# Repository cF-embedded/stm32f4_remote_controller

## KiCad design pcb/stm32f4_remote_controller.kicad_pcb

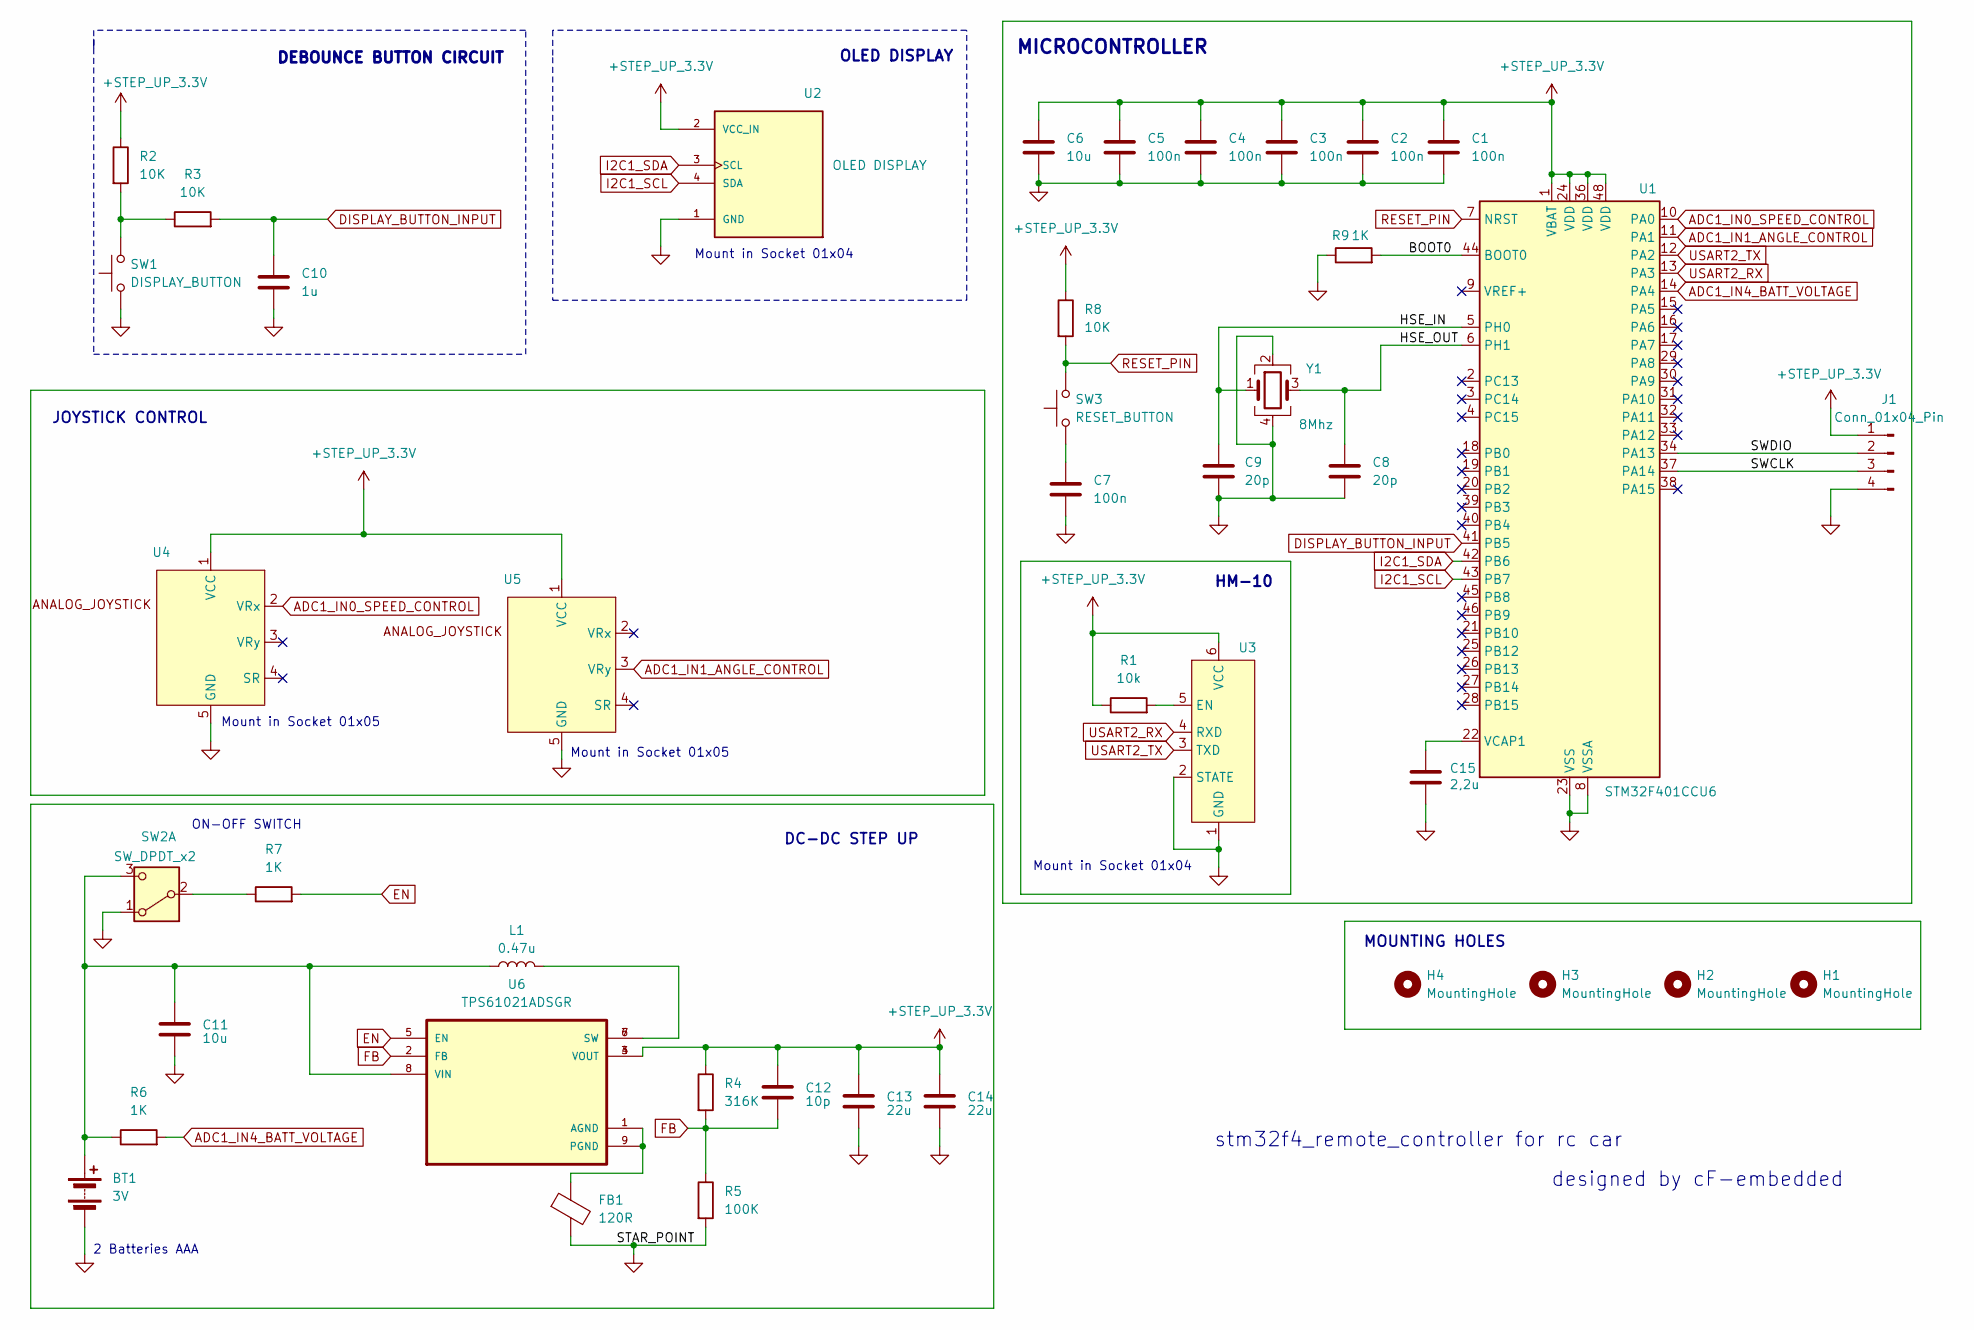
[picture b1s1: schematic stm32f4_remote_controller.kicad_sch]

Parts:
BT1: 3V; PhoenixContact_GMSTBA_2,5_2-G-7,62_1x02_P7.62mm_Horizontal
C1, C2, C3, C4, C5, C7: 100n; C_0402_1005Metric
C6, C11: 10u; C_0603_1608Metric
C8, C9: 20p; C_0402_1005Metric
C10: 1u; C_0603_1608Metric
C12: 10p; C_0402_1005Metric
C13, C14: 22u; C_0805_2012Metric
C15: 2,2u; C_0603_1608Metric
FB1: 120R; L_0603_1608Metric
H1, H2, H3, H4: MountingHole; MountingHole_2.5mm
J1: Conn_01x04_Pin; PinHeader_1x04_P2.54mm_Vertical
L1: 0.47u; L_1206_3216Metric
R1: 10k; R_0402_1005Metric
R2, R3, R8: 10K; R_0402_1005Metric
R4: 316K; R_0805_2012Metric
R5: 100K; R_0805_2012Metric
R6, R7, R9: 1K; R_0402_1005Metric
SW1: DISPLAY_BUTTON; PinHeader_1x02_P2.54mm_Vertical
SW2: SW_DPDT_x2; SW_CK_JS202011AQN_DPDT_Angled
SW3: RESET_BUTTON; SW_PUSH_6mm
U1: STM32F401CCU6; QFN-48-1EP_7x7mm_P0.5mm_EP5.6x5.6mm
U2: OLED DISPLAY; PinHeader_1x04_P2.54mm_Vertical; PARTREV 2018-09-10
U3: Molex_SL_171971-0006_1x06_P2.54mm_Vertical
U4, U5: PinHeader_1x05_P2.54mm_Vertical
U6: TPS61021ADSGR; SON50P200X200X80-9N
Y1: 8Mhz; Crystal_SMD_5032-4Pin_5.0x3.2mm

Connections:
+STEP_UP_3.3V: C1.1, C2.1, C3.1, C4.1, C5.1, C6.1, C12.1, C13.1, C14.1, J1.1, R1.1, R2.1, R4.1, R8.1, U1.1 (VBAT), U1.24 (VDD), U1.36 (VDD), U1.48 (VDD), U2.2 (VCC_IN), U3.6 (VCC), U4.1 (VCC), U5.1 (VCC), U6.3 (VOUT), U6.4 (VOUT)
/BOOT0: R9.2, U1.44 (BOOT0)
/HSE_IN: C9.1, U1.5 (PH0), Y1.1
/HSE_OUT: C8.1, U1.6 (PH1), Y1.3
/SWCLK: J1.3, U1.37 (PA14)
/SWDIO: J1.2, U1.34 (PA13)
ADC1_IN0_SPEED_CONTROL: U1.10 (PA0), U4.2 (VRx)
ADC1_IN1_ANGLE_CONTROL: U1.11 (PA1), U5.3 (VRy)
ADC1_IN4_BATT_VOLTAGE: R6.2, U1.14 (PA4)
DISPLAY_BUTTON_INPUT: C10.1, R3.2, U1.41 (PB5)
EN: R7.2, U6.5 (EN)
FB: C12.2, R4.2, R5.1, U6.2 (FB)
GND: BT1.2 (-), C1.2, C2.2, C3.2, C4.2, C5.2, C6.2, C7.2, C8.2, C9.2, C10.2, C11.2, C13.2, C14.2, C15.2, FB1.2, J1.4, R5.2, R9.1, SW1.1, SW2.1 (A), U1.8 (VSSA), U1.23 (VSS), U1.35 (VSS), U1.47 (VSS), U1.49 (VSS), U2.1 (GND), U3.1 (GND), U3.2 (STATE), U4.5 (GND), U5.5 (GND), Y1.2, Y1.4
I2C1_SCL: U1.43 (PB7), U2.4 (SDA)
I2C1_SDA: U1.42 (PB6), U2.3 (SCL)
unnamed: BT1.1 (+), C11.1, L1.1, R6.1, SW2.3 (C), U6.8 (VIN)
unnamed: C7.1, SW3.1
unnamed: L1.2, U6.6 (SW), U6.7 (SW)
unnamed: R2.2, R3.1, SW1.2
unnamed: R7.1, SW2.2 (B)
unnamed: C15.1, U1.22 (VCAP1)
unnamed: R1.2, U3.5 (EN)
unnamed: FB1.1, U6.1 (AGND), U6.9 (PGND)
RESET_PIN: R8.2, SW3.2, U1.7 (NRST)
USART2_RX: U1.13 (PA3), U3.4 (RXD)
USART2_TX: U1.12 (PA2), U3.3 (TXD)

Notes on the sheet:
MICROCONTROLLER
ON-OFF SWITCH
stm32f4_remote_controller for rc car
Mount in Socket 01x05
Mount in Socket 01x04
MOUNTING HOLES
DC-DC STEP UP
HM-10
OLED DISPLAY
2 Batteries AAA
designed by cF-embedded
DEBOUNCE BUTTON CIRCUIT
JOYSTICK CONTROL

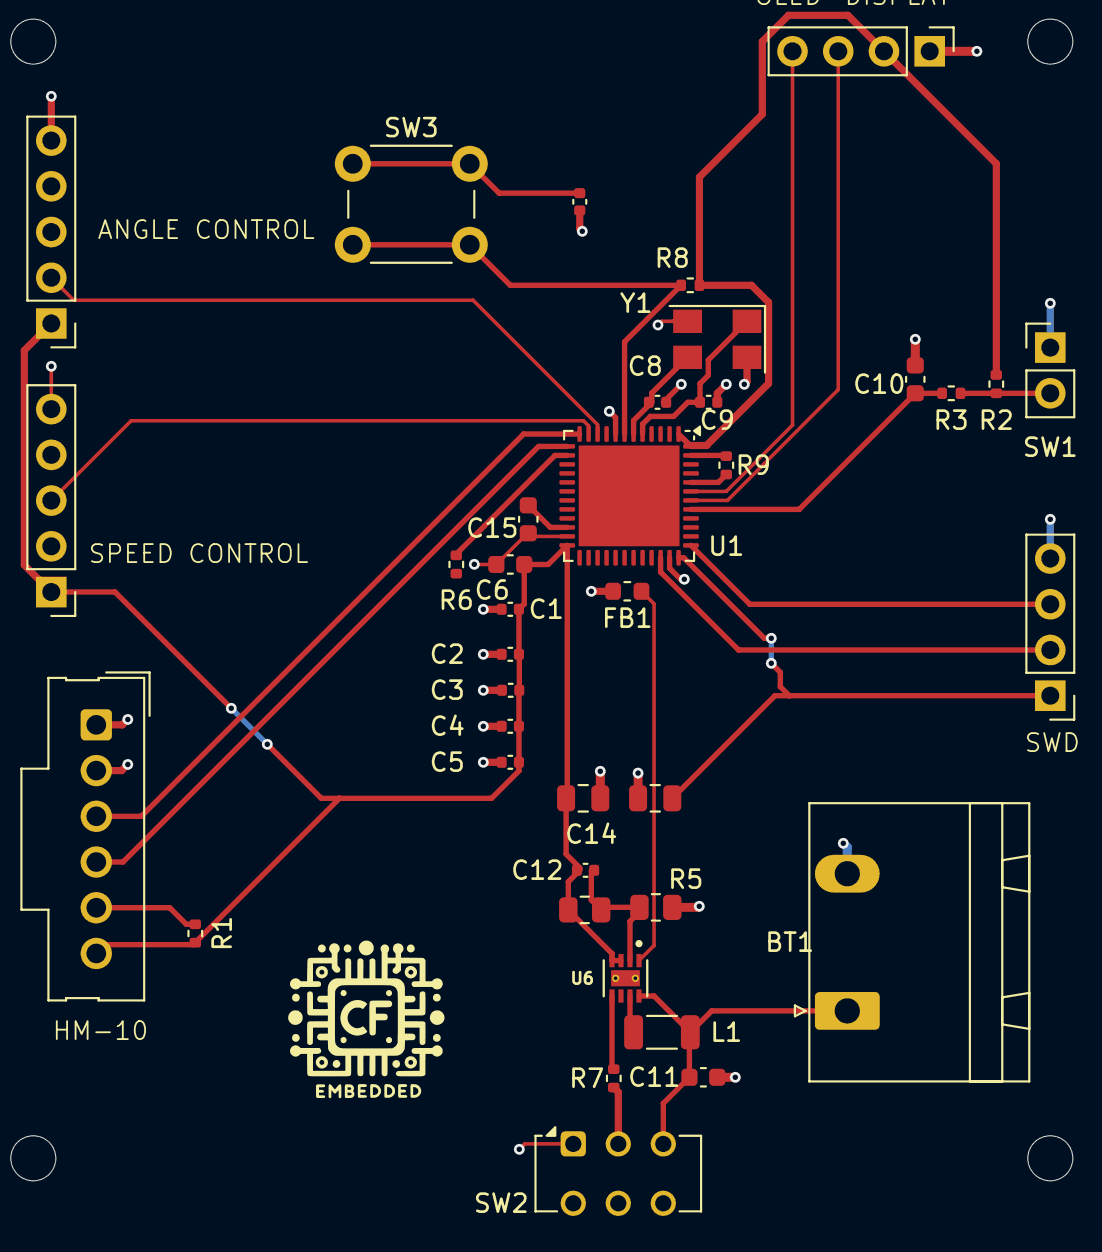
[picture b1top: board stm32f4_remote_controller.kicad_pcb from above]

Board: 2 copper layers, 42 parts (0 on the bottom side), 26 nets.

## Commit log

2024-04-29 project: add .gitignore
2024-04-29 project: add unit tests
2024-04-29 project: add stm32 files
2024-04-29 project: add .vscode files
2024-04-29 project: add .clang-format
2024-04-29 hm-10: add hm-10 files
2024-04-29 hm-10: add hm-10 files to CmakeLists.txt
2024-05-04 platform_specific: add queue isr rtos functions
2024-05-04 hm-10: add usart driver to CmakeLists.txt
2024-05-04 hm-10: add hm_10 init tasks
2024-05-04 priority: add usart irq priority
2024-05-04 hm_10_init_commands: add const array of init commands
2024-05-04 hm-10: add usart driver
2024-05-04 priority: add hm-10 init task priorities
2024-05-04 hm-10: add hm_10 send and read functions
2024-05-04 hm-10: add init task
2024-05-04 hm-10: add at commands delay
2024-05-04 initialization: add initialization of whole system
2024-05-04 i2c_master: add i2c master driver
2024-05-04 priority: add i2c irq priorities
2024-05-04 ssd1306: add ssd1306 driver
2024-05-04 display: add display files
2024-05-04 priority: add display priorities
2024-05-04 tmp 2
2024-05-05 tmp 4
2024-05-05 font_ascii_5x7: add ascii font
2024-05-05 ssd1306: add draw_char draw_string
2024-05-05 string_utils: add string utils
2024-05-05 battery_bitmap: edit battery bitmap
2024-05-05 battery_display implementation
2024-05-05 hm-10: fix hm_10_read_buf name
2024-05-06 cmake: add global cmake files
2024-05-06 test: replace GTest by Unity
2024-05-06 src: edit stm32 cmake
2024-05-06 project: add global CmakeLists for tests and stm32
2024-05-06 .vscode: add vscode json for new cmake struct
2024-05-06 adc: add adc initialization
2024-05-06 priority: add joystick controller tasks priority
2024-05-06 joystick_controller: add joystick controller tasks
2024-05-06 joystick_controller: add joystick controller files
2024-05-09 adc: add adc_to_val function
2024-05-09 initialization: add joystick_controller to initialization
2024-05-09 hm-10: add joystick tasks resume after initialization
2024-05-09 joystick_controller: add joystick_controller task implementation
2024-05-12 priority: delete unnecessary priorities
2024-05-12 hm_10: delete unnecessary task resume
2024-05-12 joystick_controller: delete unnecessary task handle
2024-05-12 joystick_controller: change control speed and angles range into percentages
2024-05-12 joystick_controller: change speed and angle send task into one task
2024-05-18 speedometer_bitmap: add speedometer bitmap
2024-05-18 display: add speedometer screen
2024-05-18 font_ascii_5x7: add ascii 5x7 font
2024-05-18 ssd1306: refactor draw bitmap
2024-05-18 display: add battery screen
2024-05-18 ssd1306: add drawing functions
2024-05-18 ssd1306: add proper initialization
2024-05-18 ssd1306: refactor ssd1306_draw_pixel
2024-05-18 battery_bitmap: add battery bitmap
2024-05-18 display: ignore snprintf
2024-05-18 initialization: add display init
2024-05-18 display: add speed from hm_10 implementation
2024-05-18 display: add display_state_machine files
2024-05-18 button: add EXTI irq during button pressed
2024-05-18 display: move screens implementation to display_state_machine
2024-05-18 button: add button driver
2024-05-18 display: change additional files location
2024-05-18 display: move types to display_state_machine_types
2024-05-18 display_state_machine: refactor display_state_machine files
2024-05-18 display: rename bitmaps files
2024-05-18 display: add display_state_machine_types file
2024-05-18 display: tasks refactor
2024-05-18 display: add display_state_machine_func files
2024-05-18 pcb: add hm-10 sym
2024-05-18 pcb: add external oled display
2024-05-18 pcb: add sections
2024-05-18 pcb: add hm-10 sch
2024-05-18 pcb: add analog joystick sym
2024-05-18 pcb: add button debounce circuit
2024-05-18 pcb: add analog joystick connection to adc
2024-05-18 pcb: add oled to sch
2024-05-18 pcb: add source supply
2024-05-18 pcb: add kicad files
2024-05-18 pcb: add footprints to elements
2024-05-18 pcb: add TPS61021 models
2024-05-18 pcb: connect vcap to gnd
2024-05-18 pcb: add reset button on sch
2024-05-18 pcb: add LTSpice dc-dc-dc_step_up simulation
2024-05-18 pcb: add TPS61021A LTSpice model
2024-05-18 pcb: add first version of pcb
2024-05-18 pcb: add dc-dc-step-up sch
2024-05-18 pcb: add values to component on sch
2024-05-18 pcb: add DC-DC STEP UP converter
2024-05-30 pcb: add ready pcb
